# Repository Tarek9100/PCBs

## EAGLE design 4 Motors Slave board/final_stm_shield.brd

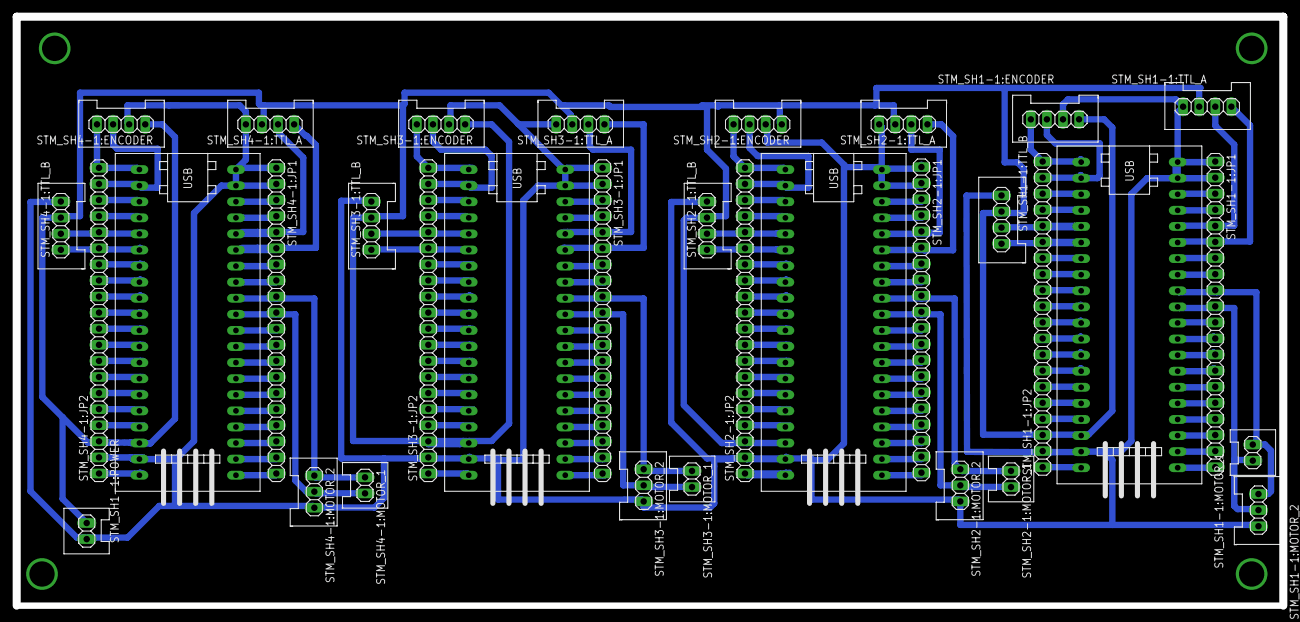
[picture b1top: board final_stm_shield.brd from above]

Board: 2 copper layers, 200.0 x 93.0 mm, 33 parts (0 on the bottom side), 146 nets.

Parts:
STM_SH1-1:ENCODER, STM_SH1-1:TTL_A, STM_SH1-1:TTL_B, STM_SH2-1:ENCODER, STM_SH2-1:TTL_A, STM_SH2-1:TTL_B, STM_SH3-1:ENCODER, STM_SH3-1:TTL_A, STM_SH3-1:TTL_B, STM_SH4-1:ENCODER, STM_SH4-1:TTL_A, STM_SH4-1:TTL_B: 1X04_DATA
STM_SH1-1:JP1, STM_SH1-1:JP2, STM_SH2-1:JP1, STM_SH2-1:JP2, STM_SH3-1:JP1, STM_SH3-1:JP2, STM_SH4-1:JP1, STM_SH4-1:JP2: 1X20
STM_SH1-1:MOTOR_1, STM_SH1-1:POWER, STM_SH2-1:MOTOR_1, STM_SH3-1:MOTOR_1, STM_SH4-1:MOTOR_1: 1X02_DATA
STM_SH1-1:MOTOR_2, STM_SH2-1:MOTOR_2, STM_SH3-1:MOTOR_2, STM_SH4-1:MOTOR_2: 1X03_DATA
STM_SH1-1:U$1, STM_SH2-1:U$1, STM_SH3-1:U$1, STM_SH4-1:U$1: STM32F103C8T6-MODULE

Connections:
5V: STM_SH1-1:ENCODER.1, STM_SH1-1:JP2.3, STM_SH1-1:POWER.2, STM_SH1-1:TTL_A.3, STM_SH1-1:TTL_B.3, STM_SH1-1:U$1.5V, STM_SH2-1:ENCODER.1, STM_SH2-1:JP2.3, STM_SH2-1:TTL_A.3, STM_SH2-1:TTL_B.3, STM_SH2-1:U$1.5V, STM_SH3-1:ENCODER.1, STM_SH3-1:JP2.3, STM_SH3-1:TTL_A.3, STM_SH3-1:TTL_B.3, STM_SH3-1:U$1.5V, STM_SH4-1:ENCODER.1, STM_SH4-1:JP2.3, STM_SH4-1:TTL_A.3, STM_SH4-1:TTL_B.3, STM_SH4-1:U$1.5V
GND: STM_SH1-1:ENCODER.2, STM_SH1-1:JP1.1, STM_SH1-1:JP1.2, STM_SH1-1:JP2.2, STM_SH1-1:MOTOR_2.3, STM_SH1-1:POWER.1, STM_SH1-1:TTL_A.4, STM_SH1-1:TTL_B.4, STM_SH1-1:U$1.GND_1, STM_SH1-1:U$1.GND_2, STM_SH1-1:U$1.GND_3, STM_SH2-1:ENCODER.2, STM_SH2-1:JP1.1, STM_SH2-1:JP1.2, STM_SH2-1:JP2.2, STM_SH2-1:MOTOR_2.3, STM_SH2-1:TTL_A.4, STM_SH2-1:TTL_B.4, STM_SH2-1:U$1.GND_1, STM_SH2-1:U$1.GND_2, STM_SH2-1:U$1.GND_3, STM_SH3-1:ENCODER.2, STM_SH3-1:JP1.1, STM_SH3-1:JP1.2, STM_SH3-1:JP2.2, STM_SH3-1:MOTOR_2.3, STM_SH3-1:TTL_A.4, STM_SH3-1:TTL_B.4, STM_SH3-1:U$1.GND_1, STM_SH3-1:U$1.GND_2, STM_SH3-1:U$1.GND_3, STM_SH4-1:ENCODER.2, STM_SH4-1:JP1.1, STM_SH4-1:JP1.2, STM_SH4-1:JP2.2, STM_SH4-1:MOTOR_2.3, STM_SH4-1:TTL_A.4, STM_SH4-1:TTL_B.4, STM_SH4-1:U$1.GND_1, STM_SH4-1:U$1.GND_2, STM_SH4-1:U$1.GND_3
STM_SH1-1:3.3V@1: STM_SH1-1:JP2.1, STM_SH1-1:U$1.3.3V_1
STM_SH1-1:3.3V@2: STM_SH1-1:JP1.3, STM_SH1-1:U$1.3.3V_2
STM_SH1-1:PA_0: STM_SH1-1:JP1.16, STM_SH1-1:U$1.PA_0
STM_SH1-1:PA_1: STM_SH1-1:JP1.15, STM_SH1-1:U$1.PA_1
STM_SH1-1:PA_2: STM_SH1-1:JP1.14, STM_SH1-1:U$1.PA_2
STM_SH1-1:PA_3: STM_SH1-1:JP1.13, STM_SH1-1:U$1.PA_3
STM_SH1-1:PA_4: STM_SH1-1:JP1.12, STM_SH1-1:U$1.PA_4
STM_SH1-1:PA_5: STM_SH1-1:JP1.11, STM_SH1-1:U$1.PA_5
STM_SH1-1:PA_6: STM_SH1-1:JP1.10, STM_SH1-1:MOTOR_1.2, STM_SH1-1:MOTOR_2.2, STM_SH1-1:U$1.PA_6
STM_SH1-1:PA_7: STM_SH1-1:JP1.9, STM_SH1-1:MOTOR_1.1, STM_SH1-1:MOTOR_2.1, STM_SH1-1:U$1.PA_7
STM_SH1-1:PA_8: STM_SH1-1:JP2.16, STM_SH1-1:TTL_B.2, STM_SH1-1:U$1.PA_8
STM_SH1-1:PA_9: STM_SH1-1:JP2.15, STM_SH1-1:TTL_B.1, STM_SH1-1:U$1.PA_9
STM_SH1-1:PA_10: STM_SH1-1:JP2.14, STM_SH1-1:U$1.PA_10
STM_SH1-1:PA_11: STM_SH1-1:JP2.13, STM_SH1-1:U$1.PA_11
STM_SH1-1:PA_12: STM_SH1-1:JP2.12, STM_SH1-1:U$1.PA_12
STM_SH1-1:PA_15: STM_SH1-1:JP2.11, STM_SH1-1:U$1.PA_15
STM_SH1-1:PB_0: STM_SH1-1:JP1.8, STM_SH1-1:U$1.PB_0
STM_SH1-1:PB_1: STM_SH1-1:JP1.7, STM_SH1-1:U$1.PB_1
STM_SH1-1:PB_3: STM_SH1-1:JP2.10, STM_SH1-1:U$1.PB_3
STM_SH1-1:PB_4: STM_SH1-1:JP2.9, STM_SH1-1:U$1.PB_4
STM_SH1-1:PB_5: STM_SH1-1:JP2.8, STM_SH1-1:U$1.PB_5
STM_SH1-1:PB_6: STM_SH1-1:JP2.7, STM_SH1-1:U$1.PB_6
STM_SH1-1:PB_7: STM_SH1-1:JP2.6, STM_SH1-1:U$1.PB_7
STM_SH1-1:PB_8: STM_SH1-1:JP2.5, STM_SH1-1:U$1.PB_8
STM_SH1-1:PB_9: STM_SH1-1:JP2.4, STM_SH1-1:U$1.PB_9
STM_SH1-1:PB_10: STM_SH1-1:JP1.6, STM_SH1-1:TTL_A.1, STM_SH1-1:U$1.PB_10
STM_SH1-1:PB_11: STM_SH1-1:JP1.5, STM_SH1-1:TTL_A.2, STM_SH1-1:U$1.PB_11
STM_SH1-1:PB_12: STM_SH1-1:ENCODER.4, STM_SH1-1:JP2.20, STM_SH1-1:U$1.PB_12
STM_SH1-1:PB_13: STM_SH1-1:ENCODER.3, STM_SH1-1:JP2.19, STM_SH1-1:U$1.PB_13
STM_SH1-1:PB_14: STM_SH1-1:JP2.18, STM_SH1-1:U$1.PB_14
STM_SH1-1:PB_15: STM_SH1-1:JP2.17, STM_SH1-1:U$1.PB_15
STM_SH1-1:PC_13: STM_SH1-1:JP1.19, STM_SH1-1:U$1.PC_13
STM_SH1-1:PC_14: STM_SH1-1:JP1.18, STM_SH1-1:U$1.PC_14
STM_SH1-1:PC_15: STM_SH1-1:JP1.17, STM_SH1-1:U$1.PC_15
STM_SH1-1:RESET: STM_SH1-1:JP1.4, STM_SH1-1:U$1.RESET
STM_SH1-1:VB: STM_SH1-1:JP1.20, STM_SH1-1:U$1.VB
STM_SH2-1:3.3V@1: STM_SH2-1:JP2.1, STM_SH2-1:U$1.3.3V_1
STM_SH2-1:3.3V@2: STM_SH2-1:JP1.3, STM_SH2-1:U$1.3.3V_2
STM_SH2-1:PA_0: STM_SH2-1:JP1.16, STM_SH2-1:U$1.PA_0
STM_SH2-1:PA_1: STM_SH2-1:JP1.15, STM_SH2-1:U$1.PA_1
STM_SH2-1:PA_2: STM_SH2-1:JP1.14, STM_SH2-1:U$1.PA_2
STM_SH2-1:PA_3: STM_SH2-1:JP1.13, STM_SH2-1:U$1.PA_3
STM_SH2-1:PA_4: STM_SH2-1:JP1.12, STM_SH2-1:U$1.PA_4
STM_SH2-1:PA_5: STM_SH2-1:JP1.11, STM_SH2-1:U$1.PA_5
STM_SH2-1:PA_6: STM_SH2-1:JP1.10, STM_SH2-1:MOTOR_1.2, STM_SH2-1:MOTOR_2.2, STM_SH2-1:U$1.PA_6
STM_SH2-1:PA_7: STM_SH2-1:JP1.9, STM_SH2-1:MOTOR_1.1, STM_SH2-1:MOTOR_2.1, STM_SH2-1:U$1.PA_7
STM_SH2-1:PA_8: STM_SH2-1:JP2.16, STM_SH2-1:TTL_B.2, STM_SH2-1:U$1.PA_8
STM_SH2-1:PA_9: STM_SH2-1:JP2.15, STM_SH2-1:TTL_B.1, STM_SH2-1:U$1.PA_9
STM_SH2-1:PA_10: STM_SH2-1:JP2.14, STM_SH2-1:U$1.PA_10
STM_SH2-1:PA_11: STM_SH2-1:JP2.13, STM_SH2-1:U$1.PA_11
STM_SH2-1:PA_12: STM_SH2-1:JP2.12, STM_SH2-1:U$1.PA_12
STM_SH2-1:PA_15: STM_SH2-1:JP2.11, STM_SH2-1:U$1.PA_15
STM_SH2-1:PB_0: STM_SH2-1:JP1.8, STM_SH2-1:U$1.PB_0
STM_SH2-1:PB_1: STM_SH2-1:JP1.7, STM_SH2-1:U$1.PB_1
STM_SH2-1:PB_3: STM_SH2-1:JP2.10, STM_SH2-1:U$1.PB_3
STM_SH2-1:PB_4: STM_SH2-1:JP2.9, STM_SH2-1:U$1.PB_4
STM_SH2-1:PB_5: STM_SH2-1:JP2.8, STM_SH2-1:U$1.PB_5
STM_SH2-1:PB_6: STM_SH2-1:JP2.7, STM_SH2-1:U$1.PB_6
STM_SH2-1:PB_7: STM_SH2-1:JP2.6, STM_SH2-1:U$1.PB_7
STM_SH2-1:PB_8: STM_SH2-1:JP2.5, STM_SH2-1:U$1.PB_8
STM_SH2-1:PB_9: STM_SH2-1:JP2.4, STM_SH2-1:U$1.PB_9
STM_SH2-1:PB_10: STM_SH2-1:JP1.6, STM_SH2-1:TTL_A.1, STM_SH2-1:U$1.PB_10
STM_SH2-1:PB_11: STM_SH2-1:JP1.5, STM_SH2-1:TTL_A.2, STM_SH2-1:U$1.PB_11
STM_SH2-1:PB_12: STM_SH2-1:ENCODER.4, STM_SH2-1:JP2.20, STM_SH2-1:U$1.PB_12
STM_SH2-1:PB_13: STM_SH2-1:ENCODER.3, STM_SH2-1:JP2.19, STM_SH2-1:U$1.PB_13
STM_SH2-1:PB_14: STM_SH2-1:JP2.18, STM_SH2-1:U$1.PB_14
STM_SH2-1:PB_15: STM_SH2-1:JP2.17, STM_SH2-1:U$1.PB_15
STM_SH2-1:PC_13: STM_SH2-1:JP1.19, STM_SH2-1:U$1.PC_13
STM_SH2-1:PC_14: STM_SH2-1:JP1.18, STM_SH2-1:U$1.PC_14
STM_SH2-1:PC_15: STM_SH2-1:JP1.17, STM_SH2-1:U$1.PC_15
STM_SH2-1:RESET: STM_SH2-1:JP1.4, STM_SH2-1:U$1.RESET
STM_SH2-1:VB: STM_SH2-1:JP1.20, STM_SH2-1:U$1.VB
STM_SH3-1:3.3V@1: STM_SH3-1:JP2.1, STM_SH3-1:U$1.3.3V_1
STM_SH3-1:3.3V@2: STM_SH3-1:JP1.3, STM_SH3-1:U$1.3.3V_2
STM_SH3-1:PA_0: STM_SH3-1:JP1.16, STM_SH3-1:U$1.PA_0
STM_SH3-1:PA_1: STM_SH3-1:JP1.15, STM_SH3-1:U$1.PA_1
STM_SH3-1:PA_2: STM_SH3-1:JP1.14, STM_SH3-1:U$1.PA_2
STM_SH3-1:PA_3: STM_SH3-1:JP1.13, STM_SH3-1:U$1.PA_3
STM_SH3-1:PA_4: STM_SH3-1:JP1.12, STM_SH3-1:U$1.PA_4
STM_SH3-1:PA_5: STM_SH3-1:JP1.11, STM_SH3-1:U$1.PA_5
STM_SH3-1:PA_6: STM_SH3-1:JP1.10, STM_SH3-1:MOTOR_1.2, STM_SH3-1:MOTOR_2.2, STM_SH3-1:U$1.PA_6
STM_SH3-1:PA_7: STM_SH3-1:JP1.9, STM_SH3-1:MOTOR_1.1, STM_SH3-1:MOTOR_2.1, STM_SH3-1:U$1.PA_7
STM_SH3-1:PA_8: STM_SH3-1:JP2.16, STM_SH3-1:TTL_B.2, STM_SH3-1:U$1.PA_8
STM_SH3-1:PA_9: STM_SH3-1:JP2.15, STM_SH3-1:TTL_B.1, STM_SH3-1:U$1.PA_9
STM_SH3-1:PA_10: STM_SH3-1:JP2.14, STM_SH3-1:U$1.PA_10
STM_SH3-1:PA_11: STM_SH3-1:JP2.13, STM_SH3-1:U$1.PA_11
STM_SH3-1:PA_12: STM_SH3-1:JP2.12, STM_SH3-1:U$1.PA_12
STM_SH3-1:PA_15: STM_SH3-1:JP2.11, STM_SH3-1:U$1.PA_15
STM_SH3-1:PB_0: STM_SH3-1:JP1.8, STM_SH3-1:U$1.PB_0
STM_SH3-1:PB_1: STM_SH3-1:JP1.7, STM_SH3-1:U$1.PB_1
STM_SH3-1:PB_3: STM_SH3-1:JP2.10, STM_SH3-1:U$1.PB_3
STM_SH3-1:PB_4: STM_SH3-1:JP2.9, STM_SH3-1:U$1.PB_4
STM_SH3-1:PB_5: STM_SH3-1:JP2.8, STM_SH3-1:U$1.PB_5
STM_SH3-1:PB_6: STM_SH3-1:JP2.7, STM_SH3-1:U$1.PB_6
STM_SH3-1:PB_7: STM_SH3-1:JP2.6, STM_SH3-1:U$1.PB_7
STM_SH3-1:PB_8: STM_SH3-1:JP2.5, STM_SH3-1:U$1.PB_8
STM_SH3-1:PB_9: STM_SH3-1:JP2.4, STM_SH3-1:U$1.PB_9
STM_SH3-1:PB_10: STM_SH3-1:JP1.6, STM_SH3-1:TTL_A.1, STM_SH3-1:U$1.PB_10
STM_SH3-1:PB_11: STM_SH3-1:JP1.5, STM_SH3-1:TTL_A.2, STM_SH3-1:U$1.PB_11
STM_SH3-1:PB_12: STM_SH3-1:ENCODER.4, STM_SH3-1:JP2.20, STM_SH3-1:U$1.PB_12
STM_SH3-1:PB_13: STM_SH3-1:ENCODER.3, STM_SH3-1:JP2.19, STM_SH3-1:U$1.PB_13
STM_SH3-1:PB_14: STM_SH3-1:JP2.18, STM_SH3-1:U$1.PB_14
STM_SH3-1:PB_15: STM_SH3-1:JP2.17, STM_SH3-1:U$1.PB_15
STM_SH3-1:PC_13: STM_SH3-1:JP1.19, STM_SH3-1:U$1.PC_13
STM_SH3-1:PC_14: STM_SH3-1:JP1.18, STM_SH3-1:U$1.PC_14
STM_SH3-1:PC_15: STM_SH3-1:JP1.17, STM_SH3-1:U$1.PC_15
STM_SH3-1:RESET: STM_SH3-1:JP1.4, STM_SH3-1:U$1.RESET
STM_SH3-1:VB: STM_SH3-1:JP1.20, STM_SH3-1:U$1.VB
STM_SH4-1:3.3V@1: STM_SH4-1:JP2.1, STM_SH4-1:U$1.3.3V_1
STM_SH4-1:3.3V@2: STM_SH4-1:JP1.3, STM_SH4-1:U$1.3.3V_2
STM_SH4-1:PA_0: STM_SH4-1:JP1.16, STM_SH4-1:U$1.PA_0
STM_SH4-1:PA_1: STM_SH4-1:JP1.15, STM_SH4-1:U$1.PA_1
STM_SH4-1:PA_2: STM_SH4-1:JP1.14, STM_SH4-1:U$1.PA_2
STM_SH4-1:PA_3: STM_SH4-1:JP1.13, STM_SH4-1:U$1.PA_3
STM_SH4-1:PA_4: STM_SH4-1:JP1.12, STM_SH4-1:U$1.PA_4
STM_SH4-1:PA_5: STM_SH4-1:JP1.11, STM_SH4-1:U$1.PA_5
STM_SH4-1:PA_6: STM_SH4-1:JP1.10, STM_SH4-1:MOTOR_1.2, STM_SH4-1:MOTOR_2.2, STM_SH4-1:U$1.PA_6
STM_SH4-1:PA_7: STM_SH4-1:JP1.9, STM_SH4-1:MOTOR_1.1, STM_SH4-1:MOTOR_2.1, STM_SH4-1:U$1.PA_7
STM_SH4-1:PA_8: STM_SH4-1:JP2.16, STM_SH4-1:TTL_B.2, STM_SH4-1:U$1.PA_8
STM_SH4-1:PA_9: STM_SH4-1:JP2.15, STM_SH4-1:TTL_B.1, STM_SH4-1:U$1.PA_9
STM_SH4-1:PA_10: STM_SH4-1:JP2.14, STM_SH4-1:U$1.PA_10
STM_SH4-1:PA_11: STM_SH4-1:JP2.13, STM_SH4-1:U$1.PA_11
STM_SH4-1:PA_12: STM_SH4-1:JP2.12, STM_SH4-1:U$1.PA_12
STM_SH4-1:PA_15: STM_SH4-1:JP2.11, STM_SH4-1:U$1.PA_15
STM_SH4-1:PB_0: STM_SH4-1:JP1.8, STM_SH4-1:U$1.PB_0
STM_SH4-1:PB_1: STM_SH4-1:JP1.7, STM_SH4-1:U$1.PB_1
STM_SH4-1:PB_3: STM_SH4-1:JP2.10, STM_SH4-1:U$1.PB_3
STM_SH4-1:PB_4: STM_SH4-1:JP2.9, STM_SH4-1:U$1.PB_4
STM_SH4-1:PB_5: STM_SH4-1:JP2.8, STM_SH4-1:U$1.PB_5
STM_SH4-1:PB_6: STM_SH4-1:JP2.7, STM_SH4-1:U$1.PB_6
STM_SH4-1:PB_7: STM_SH4-1:JP2.6, STM_SH4-1:U$1.PB_7
STM_SH4-1:PB_8: STM_SH4-1:JP2.5, STM_SH4-1:U$1.PB_8
STM_SH4-1:PB_9: STM_SH4-1:JP2.4, STM_SH4-1:U$1.PB_9
STM_SH4-1:PB_10: STM_SH4-1:JP1.6, STM_SH4-1:TTL_A.1, STM_SH4-1:U$1.PB_10
STM_SH4-1:PB_11: STM_SH4-1:JP1.5, STM_SH4-1:TTL_A.2, STM_SH4-1:U$1.PB_11
STM_SH4-1:PB_12: STM_SH4-1:ENCODER.4, STM_SH4-1:JP2.20, STM_SH4-1:U$1.PB_12
STM_SH4-1:PB_13: STM_SH4-1:ENCODER.3, STM_SH4-1:JP2.19, STM_SH4-1:U$1.PB_13
STM_SH4-1:PB_14: STM_SH4-1:JP2.18, STM_SH4-1:U$1.PB_14
STM_SH4-1:PB_15: STM_SH4-1:JP2.17, STM_SH4-1:U$1.PB_15
STM_SH4-1:PC_13: STM_SH4-1:JP1.19, STM_SH4-1:U$1.PC_13
STM_SH4-1:PC_14: STM_SH4-1:JP1.18, STM_SH4-1:U$1.PC_14
STM_SH4-1:PC_15: STM_SH4-1:JP1.17, STM_SH4-1:U$1.PC_15
STM_SH4-1:RESET: STM_SH4-1:JP1.4, STM_SH4-1:U$1.RESET
STM_SH4-1:VB: STM_SH4-1:JP1.20, STM_SH4-1:U$1.VB

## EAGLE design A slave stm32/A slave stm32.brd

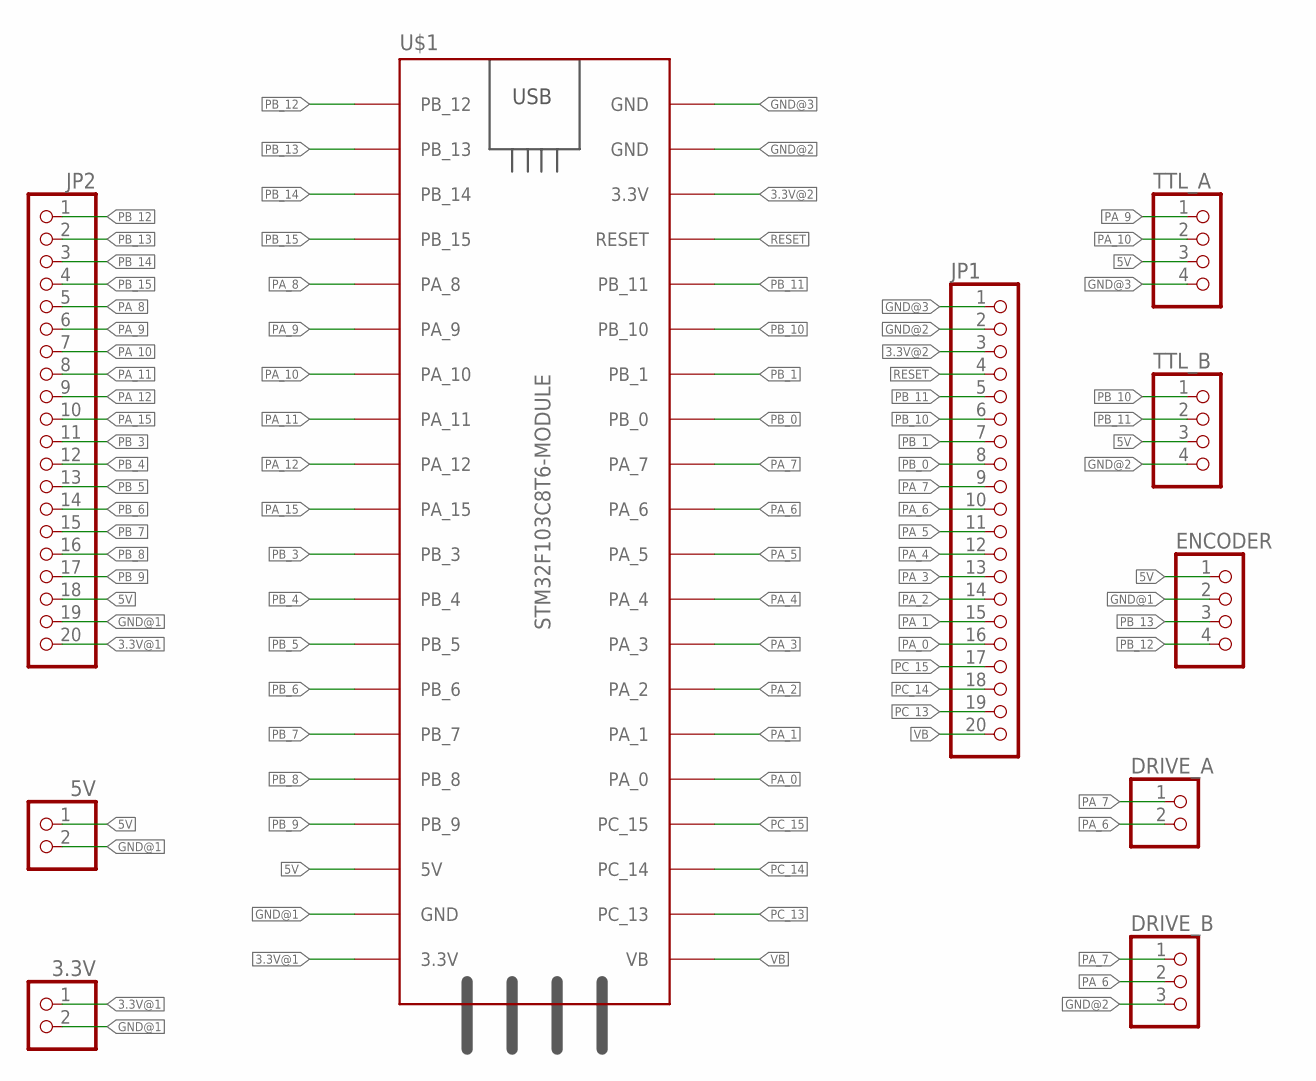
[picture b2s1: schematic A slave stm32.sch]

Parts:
3.3V, 5V: PINHD-2_DATA; 1X02_DATA
DRIVE_A: PINHD-2_DATA; 1X02_DATA
DRIVE_B: PINHD-3_DATA; 1X03_DATA
ENCODER: PINHD-4_DATA; 1X04_DATA
JP1, JP2: PINHD-1X20; 1X20
TTL_A: PINHD-4_DATA; 1X04_DATA
TTL_B: PINHD-4_DATA; 1X04_DATA
U$1: STM32F103C8T6-MODULE

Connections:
3.3V@1: 3.3V.1, JP2.20, U$1.3.3V_1 (3.3V)
3.3V@2: JP1.3, U$1.3.3V_2 (3.3V)
5V: 5V.1, ENCODER.1, JP2.18, TTL_A.3, TTL_B.3, U$1.5V
GND@1: 3.3V.2, 5V.2, ENCODER.2, JP2.19, U$1.GND_1 (GND)
GND@2: DRIVE_B.3, JP1.2, TTL_B.4, U$1.GND_2 (GND)
GND@3: JP1.1, TTL_A.4, U$1.GND_3 (GND)
PA_0: JP1.16, U$1.PA_0
PA_1: JP1.15, U$1.PA_1
PA_2: JP1.14, U$1.PA_2
PA_3: JP1.13, U$1.PA_3
PA_4: JP1.12, U$1.PA_4
PA_5: JP1.11, U$1.PA_5
PA_6: DRIVE_A.2, DRIVE_B.2, JP1.10, U$1.PA_6
PA_7: DRIVE_A.1, DRIVE_B.1, JP1.9, U$1.PA_7
PA_8: JP2.5, U$1.PA_8
PA_9: JP2.6, TTL_A.1, U$1.PA_9
PA_10: JP2.7, TTL_A.2, U$1.PA_10
PA_11: JP2.8, U$1.PA_11
PA_12: JP2.9, U$1.PA_12
PA_15: JP2.10, U$1.PA_15
PB_0: JP1.8, U$1.PB_0
PB_1: JP1.7, U$1.PB_1
PB_3: JP2.11, U$1.PB_3
PB_4: JP2.12, U$1.PB_4
PB_5: JP2.13, U$1.PB_5
PB_6: JP2.14, U$1.PB_6
PB_7: JP2.15, U$1.PB_7
PB_8: JP2.16, U$1.PB_8
PB_9: JP2.17, U$1.PB_9
PB_10: JP1.6, TTL_B.1, U$1.PB_10
PB_11: JP1.5, TTL_B.2, U$1.PB_11
PB_12: ENCODER.4, JP2.1, U$1.PB_12
PB_13: ENCODER.3, JP2.2, U$1.PB_13
PB_14: JP2.3, U$1.PB_14
PB_15: JP2.4, U$1.PB_15
PC_13: JP1.19, U$1.PC_13
PC_14: JP1.18, U$1.PC_14
PC_15: JP1.17, U$1.PC_15
RESET: JP1.4, U$1.RESET
VB: JP1.20, U$1.VB

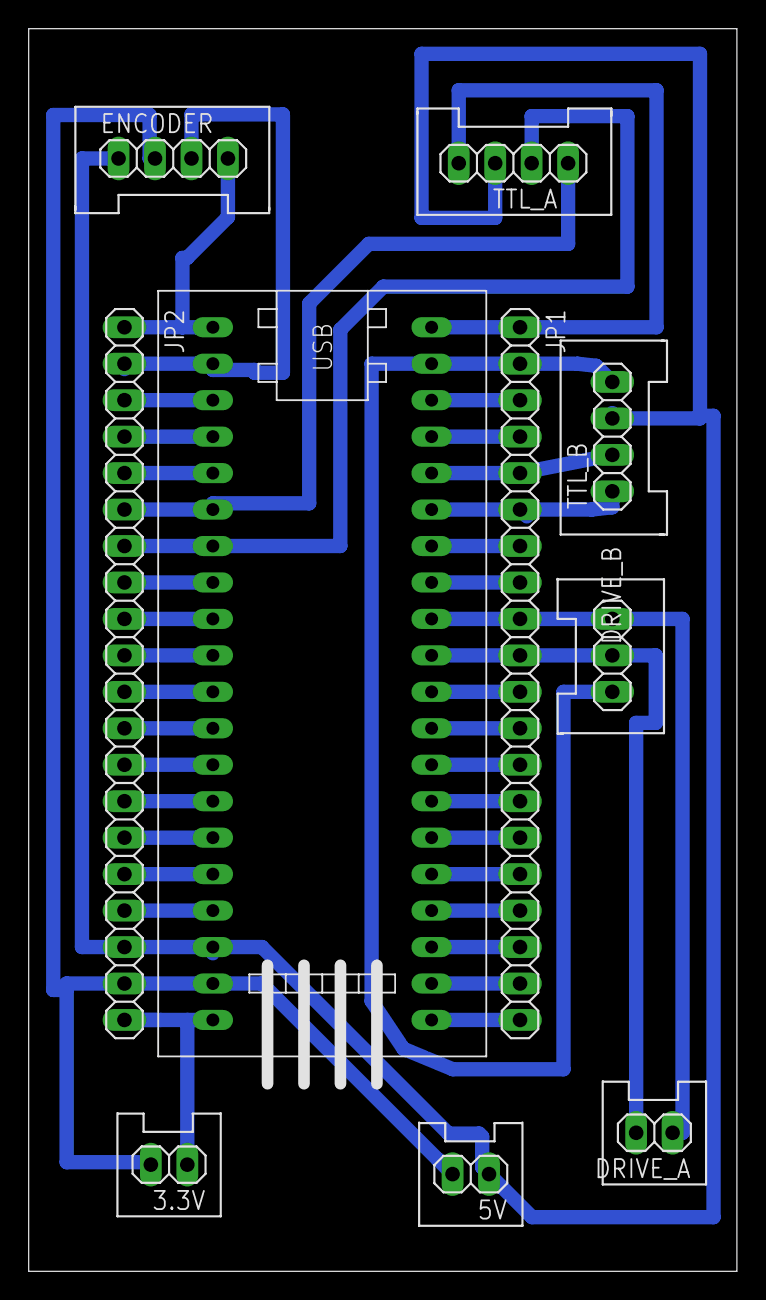
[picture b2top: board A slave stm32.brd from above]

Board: 2 copper layers, 49.3 x 86.6 mm, 10 parts (0 on the bottom side), 40 nets.

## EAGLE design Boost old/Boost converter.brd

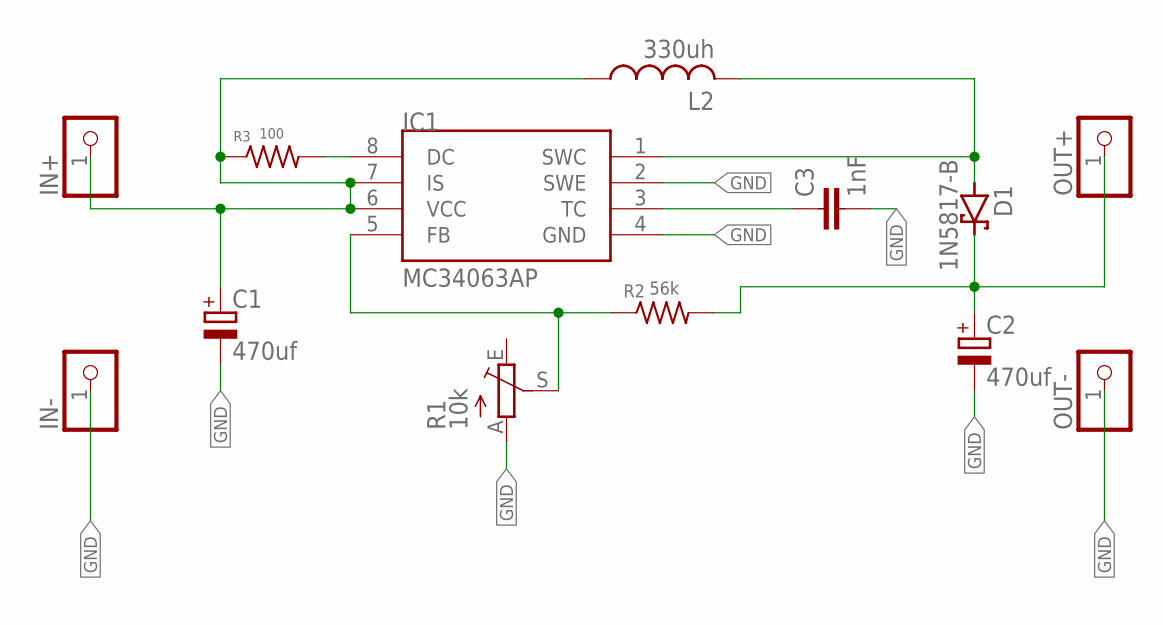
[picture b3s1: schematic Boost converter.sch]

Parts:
C1, C2: 470uf; E3,5-8
C3: 1nF; C025-025X050
D1: 1N5817-B; DO41-7.6
IC1: MC34063AP; DIL08
IN+: PINHD-1X1; 1X01
IN-: PINHD-1X1; 1X01
L2: 330uh; 0207/10
OUT+: PINHD-1X1; 1X01
OUT-: PINHD-1X1; 1X01
R1: 10k; CA6V
R2: 56k; 0204/7
R3: 100; 0204/7

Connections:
GND: C1.-, C2.-, C3.2, IC1.2 (SWE), IC1.4 (GND), IN-.1, OUT-.1, R1.A
IN: C2.+, D1.C, OUT+.1, R2.2
unnamed: C1.+, IC1.6 (VCC), IC1.7 (IS), IN+.1, L2.1, R3.1
unnamed: D1.A, IC1.1 (SWC), L2.2
unnamed: IC1.5 (FB), R1.S, R2.1
unnamed: C3.1, IC1.3 (TC)
unnamed: IC1.8 (DC), R3.2

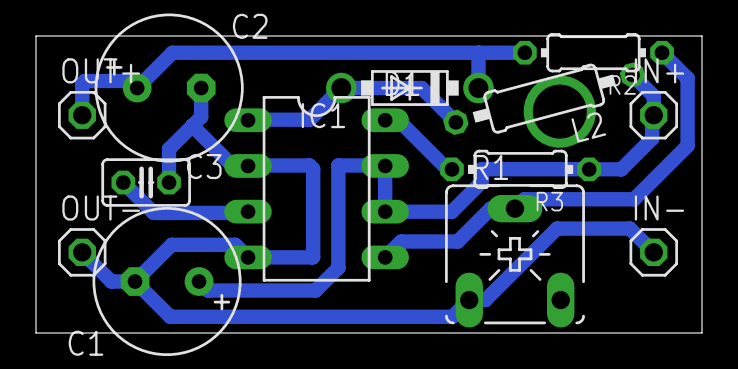
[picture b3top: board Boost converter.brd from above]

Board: 2 copper layers, 37.0 x 16.5 mm, 13 parts (0 on the bottom side), 7 nets.

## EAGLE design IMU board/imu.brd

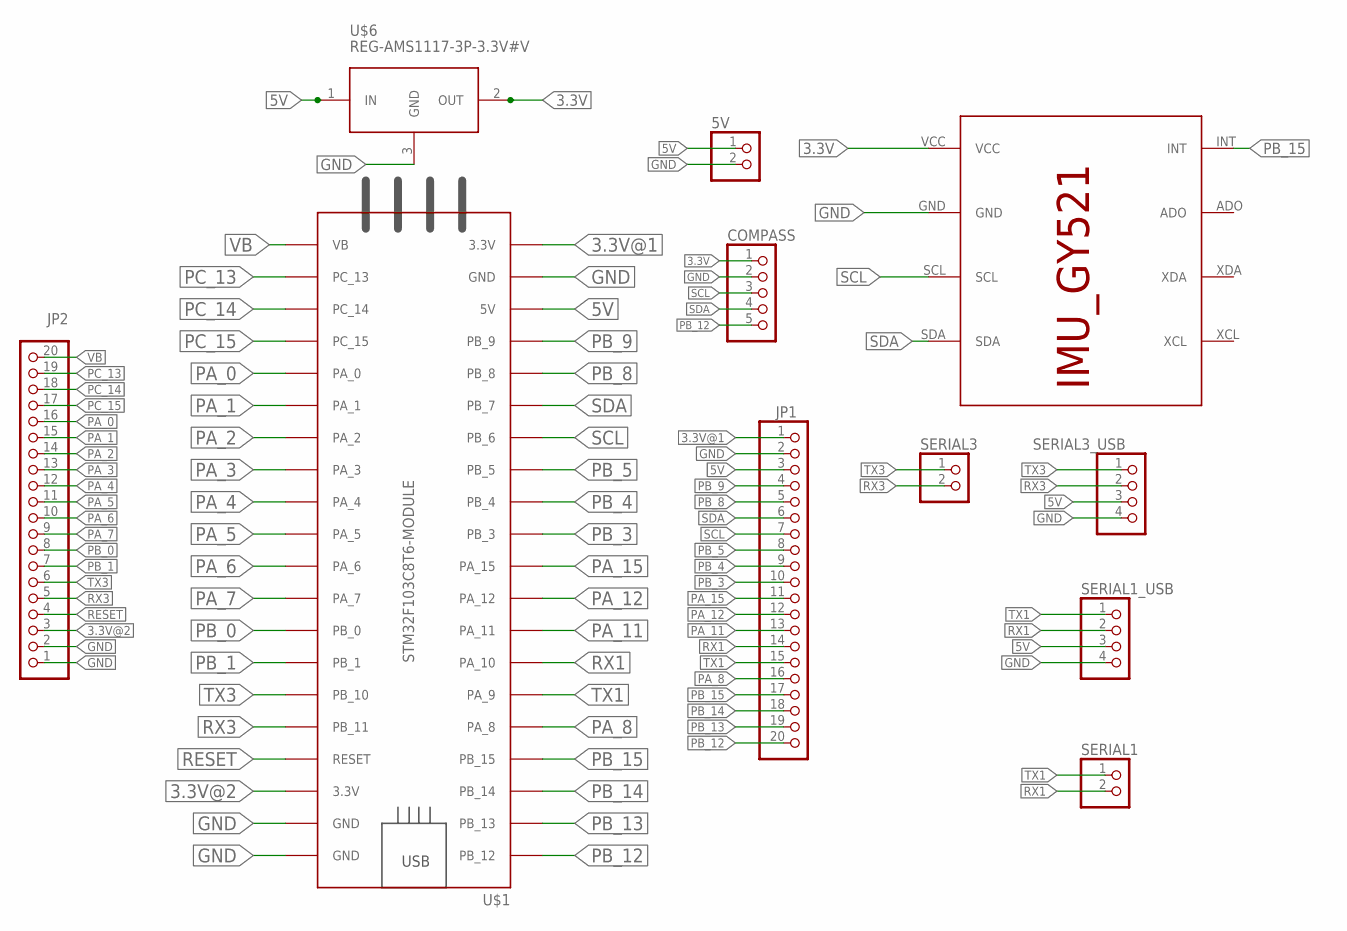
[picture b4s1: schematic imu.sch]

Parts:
5V: PINHD-2_DATA; 1X02_DATA
COMPASS: PINHD-1X5; 1X05
JP1, JP2: PINHD-1X20; 1X20
SERIAL1, SERIAL3: PINHD-2_DATA; 1X02_DATA
SERIAL1_USB, SERIAL3_USB: PINHD-4_DATA; 1X04_DATA
U$1: STM32F103C8T6-MODULE
U$2: IMU_ROBOCON_GY521; IMU_GY521
U$6: REG-AMS1117-3P-3.3V#V; REG-AMS1117-3P#V

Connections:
3.3V: COMPASS.1, U$2.VCC, U$6.2 (OUT)
3.3V@1: JP1.1, U$1.3.3V_1 (3.3V)
3.3V@2: JP2.3, U$1.3.3V_2 (3.3V)
5V: 5V.1, JP1.3, SERIAL1_USB.3, SERIAL3_USB.3, U$1.5V, U$6.1 (IN)
GND: 5V.2, COMPASS.2, JP1.2, JP2.1, JP2.2, SERIAL1_USB.4, SERIAL3_USB.4, U$1.GND_1 (GND), U$1.GND_2 (GND), U$1.GND_3 (GND), U$2.GND, U$6.3 (GND)
PA_0: JP2.16, U$1.PA_0
PA_1: JP2.15, U$1.PA_1
PA_2: JP2.14, U$1.PA_2
PA_3: JP2.13, U$1.PA_3
PA_4: JP2.12, U$1.PA_4
PA_5: JP2.11, U$1.PA_5
PA_6: JP2.10, U$1.PA_6
PA_7: JP2.9, U$1.PA_7
PA_8: JP1.16, U$1.PA_8
PA_11: JP1.13, U$1.PA_11
PA_12: JP1.12, U$1.PA_12
PA_15: JP1.11, U$1.PA_15
PB_0: JP2.8, U$1.PB_0
PB_1: JP2.7, U$1.PB_1
PB_3: JP1.10, U$1.PB_3
PB_4: JP1.9, U$1.PB_4
PB_5: JP1.8, U$1.PB_5
PB_8: JP1.5, U$1.PB_8
PB_9: JP1.4, U$1.PB_9
PB_12: COMPASS.5, JP1.20, U$1.PB_12
PB_13: JP1.19, U$1.PB_13
PB_14: JP1.18, U$1.PB_14
PB_15: JP1.17, U$1.PB_15, U$2.INT
PC_13: JP2.19, U$1.PC_13
PC_14: JP2.18, U$1.PC_14
PC_15: JP2.17, U$1.PC_15
RESET: JP2.4, U$1.RESET
RX1: JP1.14, SERIAL1.2, SERIAL1_USB.2, U$1.PA_10
RX3: JP2.5, SERIAL3.2, SERIAL3_USB.2, U$1.PB_11
SCL: COMPASS.3, JP1.7, U$1.PB_6, U$2.SCL
SDA: COMPASS.4, JP1.6, U$1.PB_7, U$2.SDA
TX1: JP1.15, SERIAL1.1, SERIAL1_USB.1, U$1.PA_9
TX3: JP2.6, SERIAL3.1, SERIAL3_USB.1, U$1.PB_10
VB: JP2.20, U$1.VB

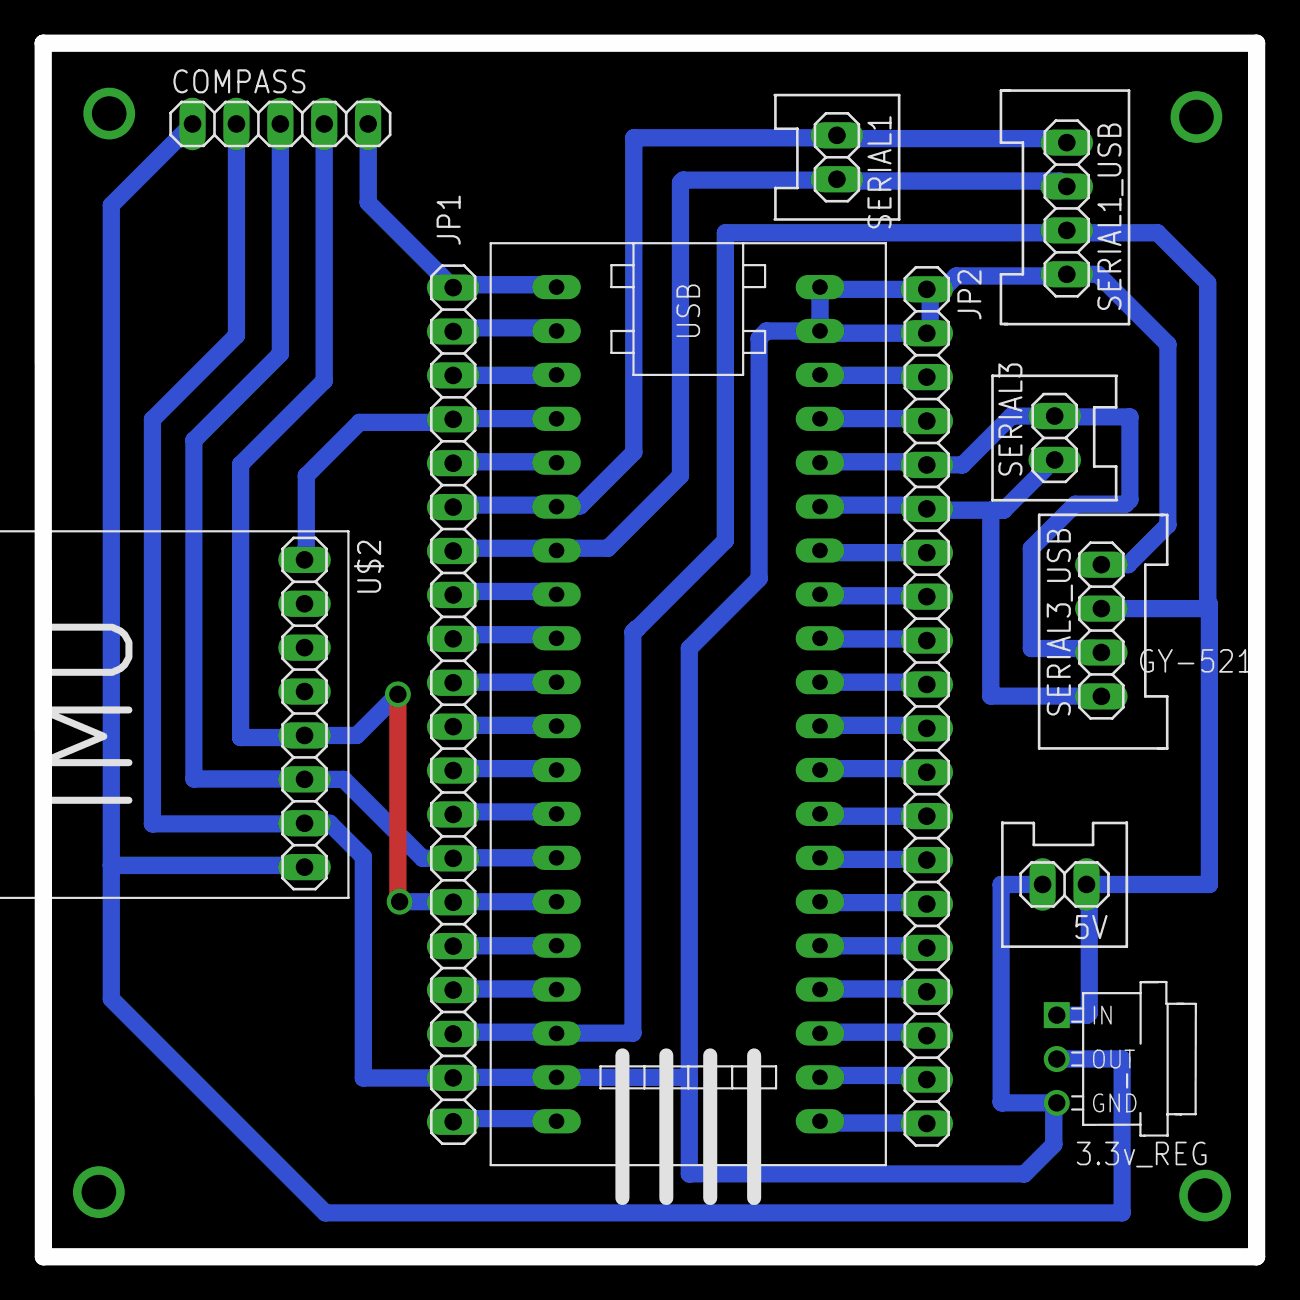
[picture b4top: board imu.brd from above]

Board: 2 copper layers, 70.2 x 70.2 mm, 11 parts (0 on the bottom side), 39 nets.

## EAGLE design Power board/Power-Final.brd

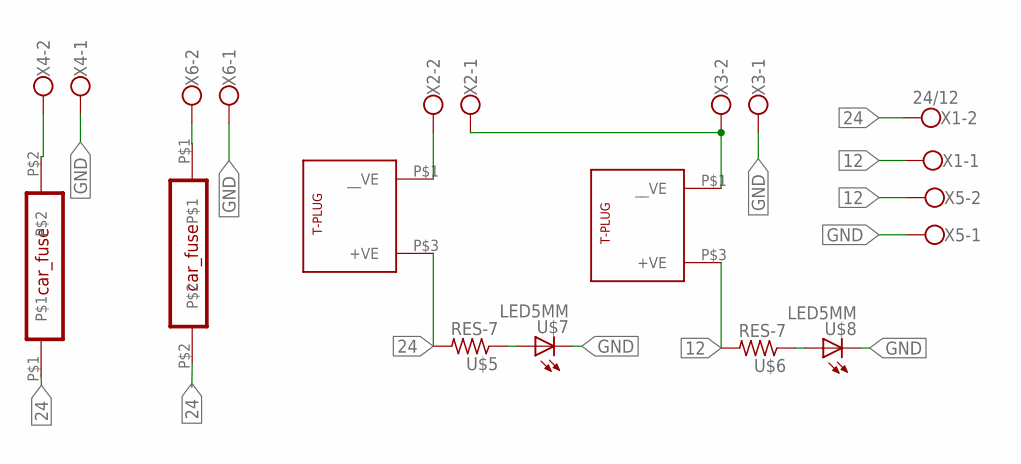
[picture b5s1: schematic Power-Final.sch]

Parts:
U$1, U$2: CAR_FUSE
U$3, U$4: T_CONNECTOR; T-PLUG
U$5, U$6: RES-7; 0204/7
U$7, U$8: LED5MM
X1: 24/12; W239-302
X2, X3, X4, X5, X6: ROSTA.POWER; W239-302

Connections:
12: U$4.P$3 (+VE), U$6.2, X1.1, X5.2
24: U$1.P$1, U$2.P$2, U$3.P$3 (+VE), U$5.2, X1.2
GND: U$7.K (C), U$8.K (C), X3.1, X4.1, X5.1, X6.1
unnamed: U$3.P$1 (__VE), X2.2
unnamed: U$2.P$1, X6.2
unnamed: U$5.1, U$7.A
unnamed: U$4.P$1 (__VE), X2.1, X3.2
unnamed: U$6.1, U$8.A
unnamed: U$1.P$2, X4.2

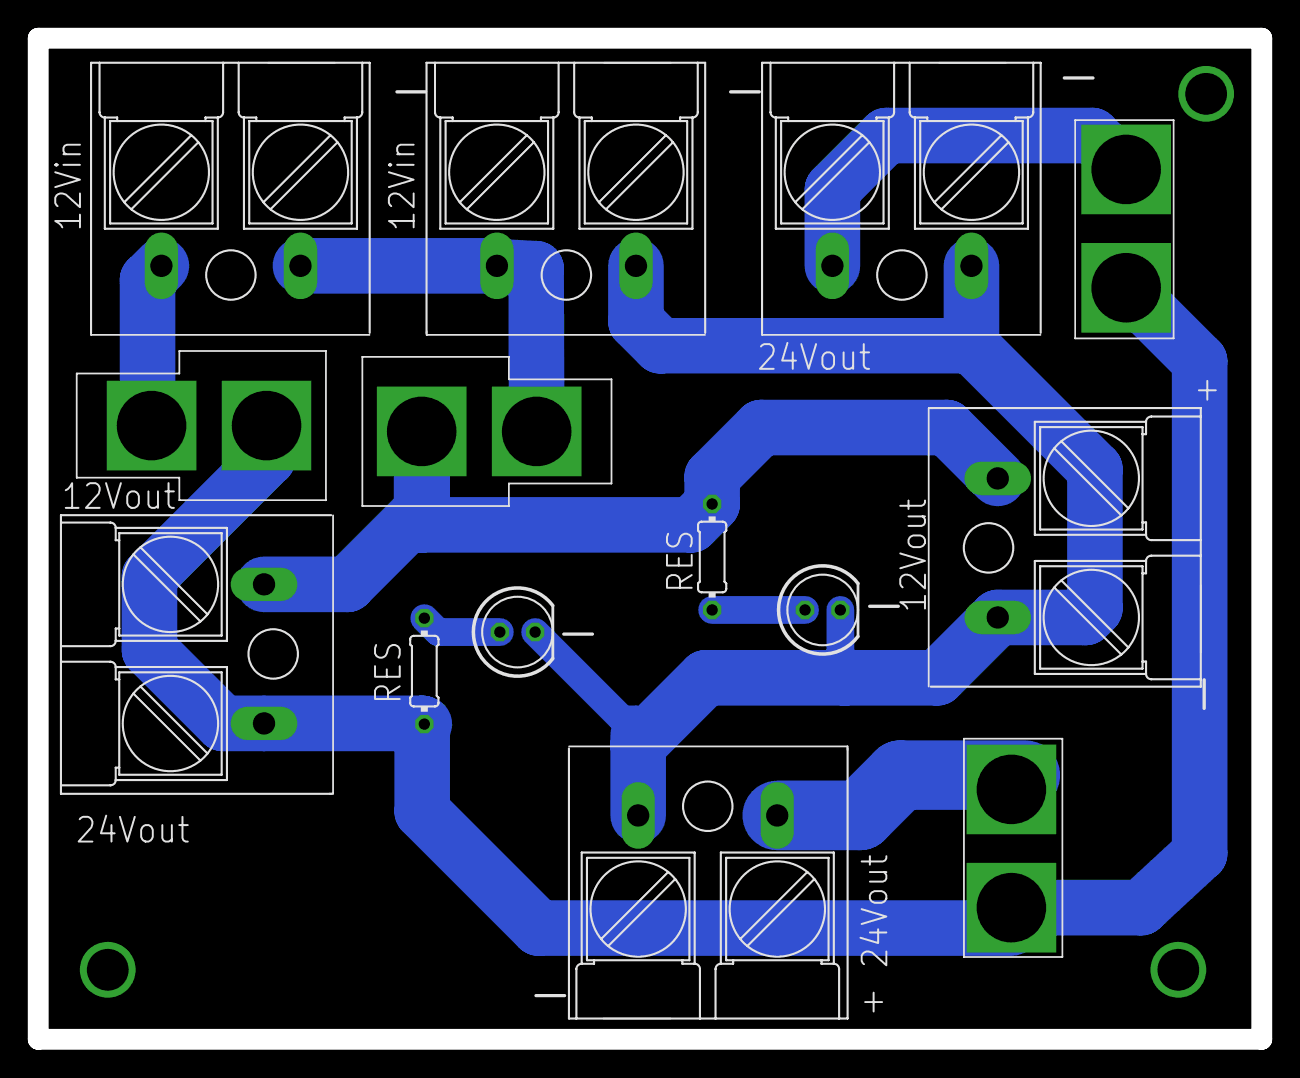
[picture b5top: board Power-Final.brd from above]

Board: 2 copper layers, 88.0 x 72.0 mm, 14 parts (0 on the bottom side), 9 nets.

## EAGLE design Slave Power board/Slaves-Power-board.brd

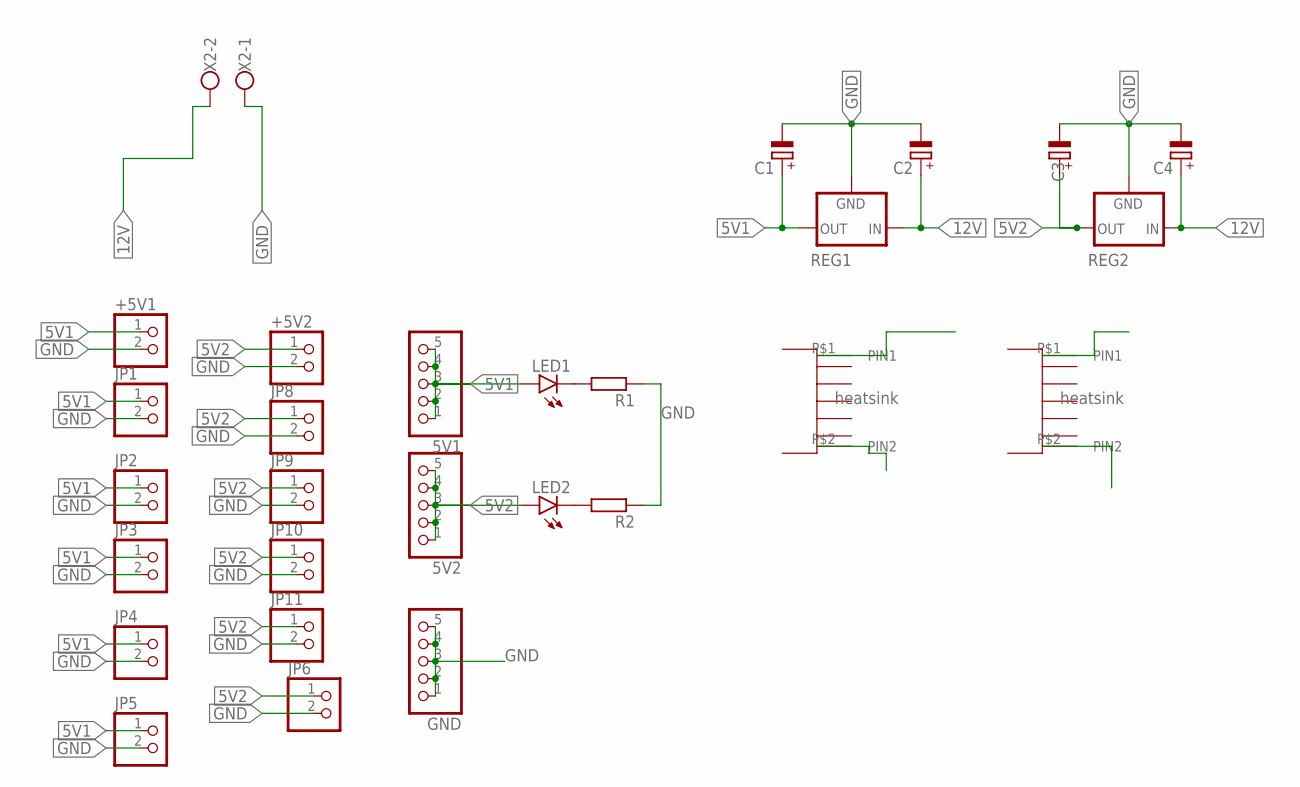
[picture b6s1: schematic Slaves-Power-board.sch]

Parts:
5V1, 5V2: PINHD-1X5; 1X05
+5V1, +5V2: PINHD-2_DATA; 1X02_DATA
C1, C2, C3, C4: CAP_POL; E3,5-8
GND: PINHD-1X5; 1X05
JP1, JP2, JP3, JP4, JP5, JP6, JP8, JP9, JP10, JP11: PINHD-2_DATA; 1X02_DATA
LED1, LED2: LED5MM
R1, R2: R-EU_0204/7; 0204/7
REG1, REG2: 78XXS
U$1, U$2: HEAT-SINK; HEAT_SINK
X2: ROSTA.POWER; W239-302

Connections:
5V1: 5V1.1, 5V1.2, 5V1.3, 5V1.4, 5V1.5, +5V1.1, C1.+, JP1.1, JP2.1, JP3.1, JP4.1, JP5.1, LED1.A, REG1.OUT
5V2: 5V2.1, 5V2.2, 5V2.3, 5V2.4, 5V2.5, +5V2.1, C3.+, JP6.1, JP8.1, JP9.1, JP10.1, JP11.1, LED2.A, REG2.OUT
12V: C2.+, C4.+, REG1.IN, REG2.IN, X2.2
GND: +5V1.2, +5V2.2, C1.-, C2.-, C3.-, C4.-, GND.1, GND.2, GND.3, GND.4, GND.5, JP1.2, JP2.2, JP3.2, JP4.2, JP5.2, JP6.2, JP8.2, JP9.2, JP10.2, JP11.2, R1.1, R2.1, REG1.GND, REG2.GND, X2.1
unnamed: LED1.K (C), R1.2
unnamed: LED2.K (C), R2.2

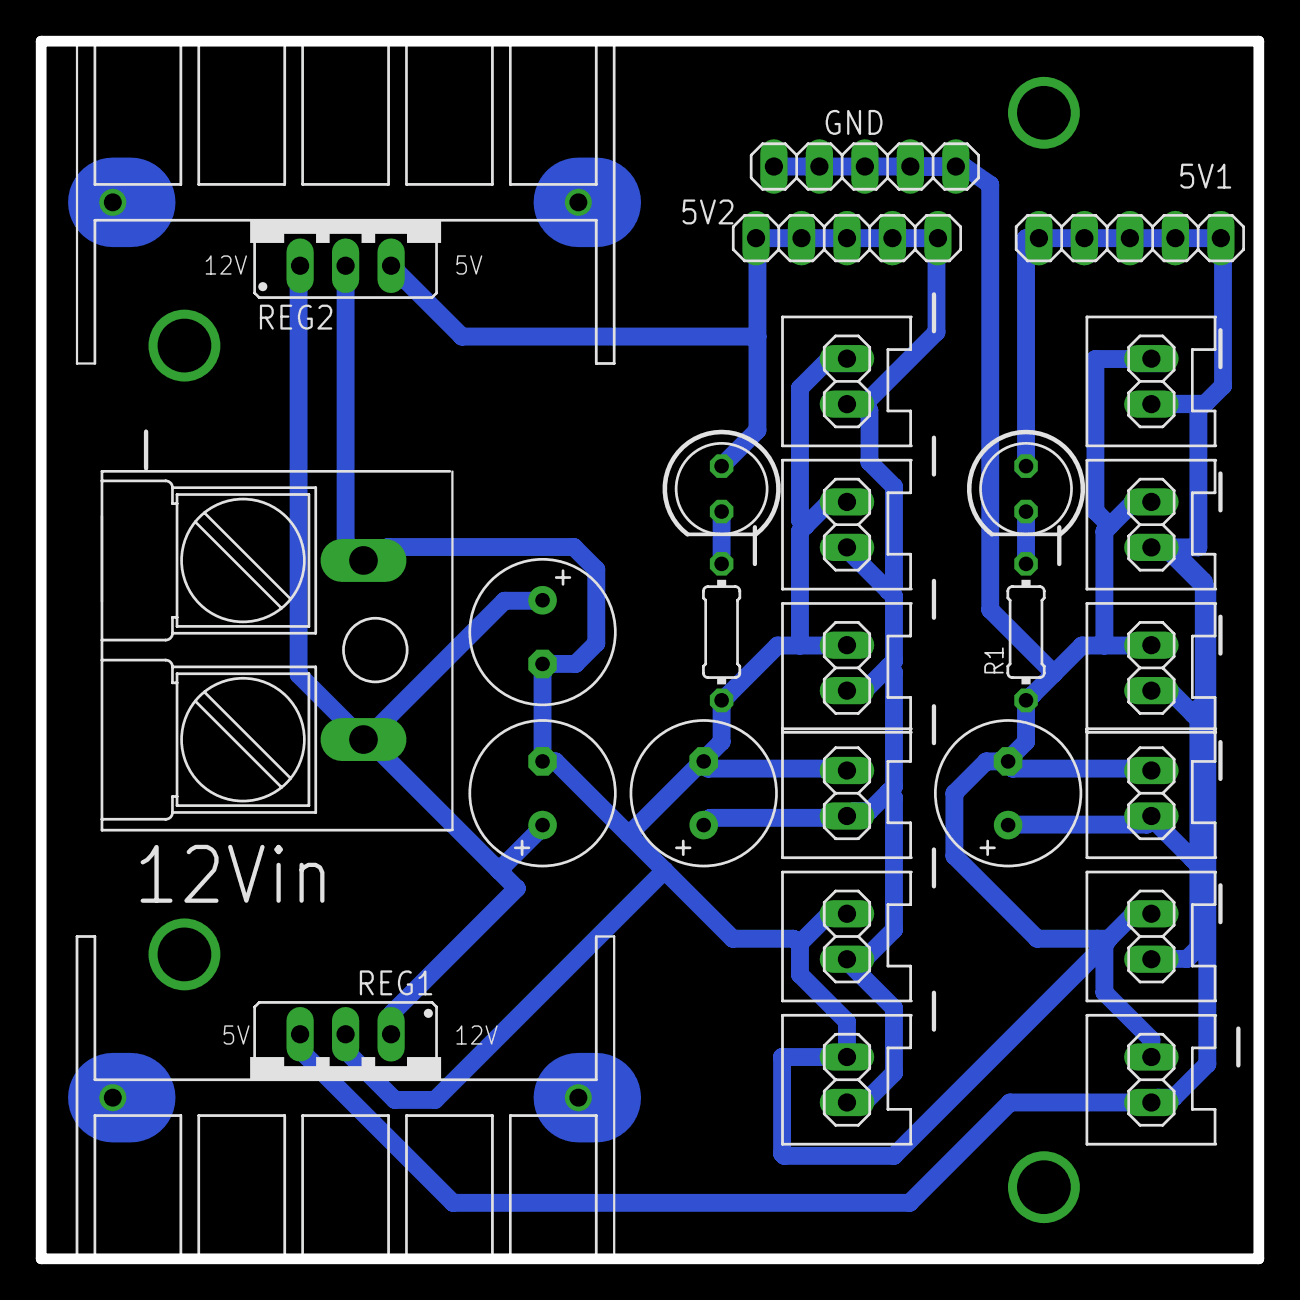
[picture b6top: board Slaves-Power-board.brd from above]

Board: 2 copper layers, 68.0 x 68.0 mm, 28 parts (0 on the bottom side), 6 nets.
